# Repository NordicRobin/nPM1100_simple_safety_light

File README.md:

The nPM1100 simple safety light is a concept sketch for using the nPM1100's "ship mode" as the on/off switch for a 
rechargeable bicycle light or other small flashlight. This gives it the simple button-press activation we're used to from 
this type of device, without the need for a microcontroller. \
\
Many rechargeable bicycle lights [needs citation] use some sort of microcontroller to control the charging and on/off functionality, 
as well as different blinking modes of the LEDs on the bicycle lights. In my experience, these microcontrollers tend to drain 
the battery of the light when left unused for a period of time. By using the nPM1100's ship mode
as a power-down mode, the light consumes only 0.45 uA while powered off. This would also be the case if a microcontroller was included in the design, as the 
nPM1100 ship mode cuts power to all devices it's powering while in this mode. \
\
As an extra challenge, the nPM1100's inputs for entering and exiting ship mode have opposite polarities, therefore a simple PNP bipolar junction transistor (BJT) is included to 
flip the polarity of the button press, when the BJT is powered by the nPM1100's regulator. The BJT adds to the current consumption of the light while the circuit is powered on, 
but does not affect the 0.45 uA current draw of the system while in ship mode.

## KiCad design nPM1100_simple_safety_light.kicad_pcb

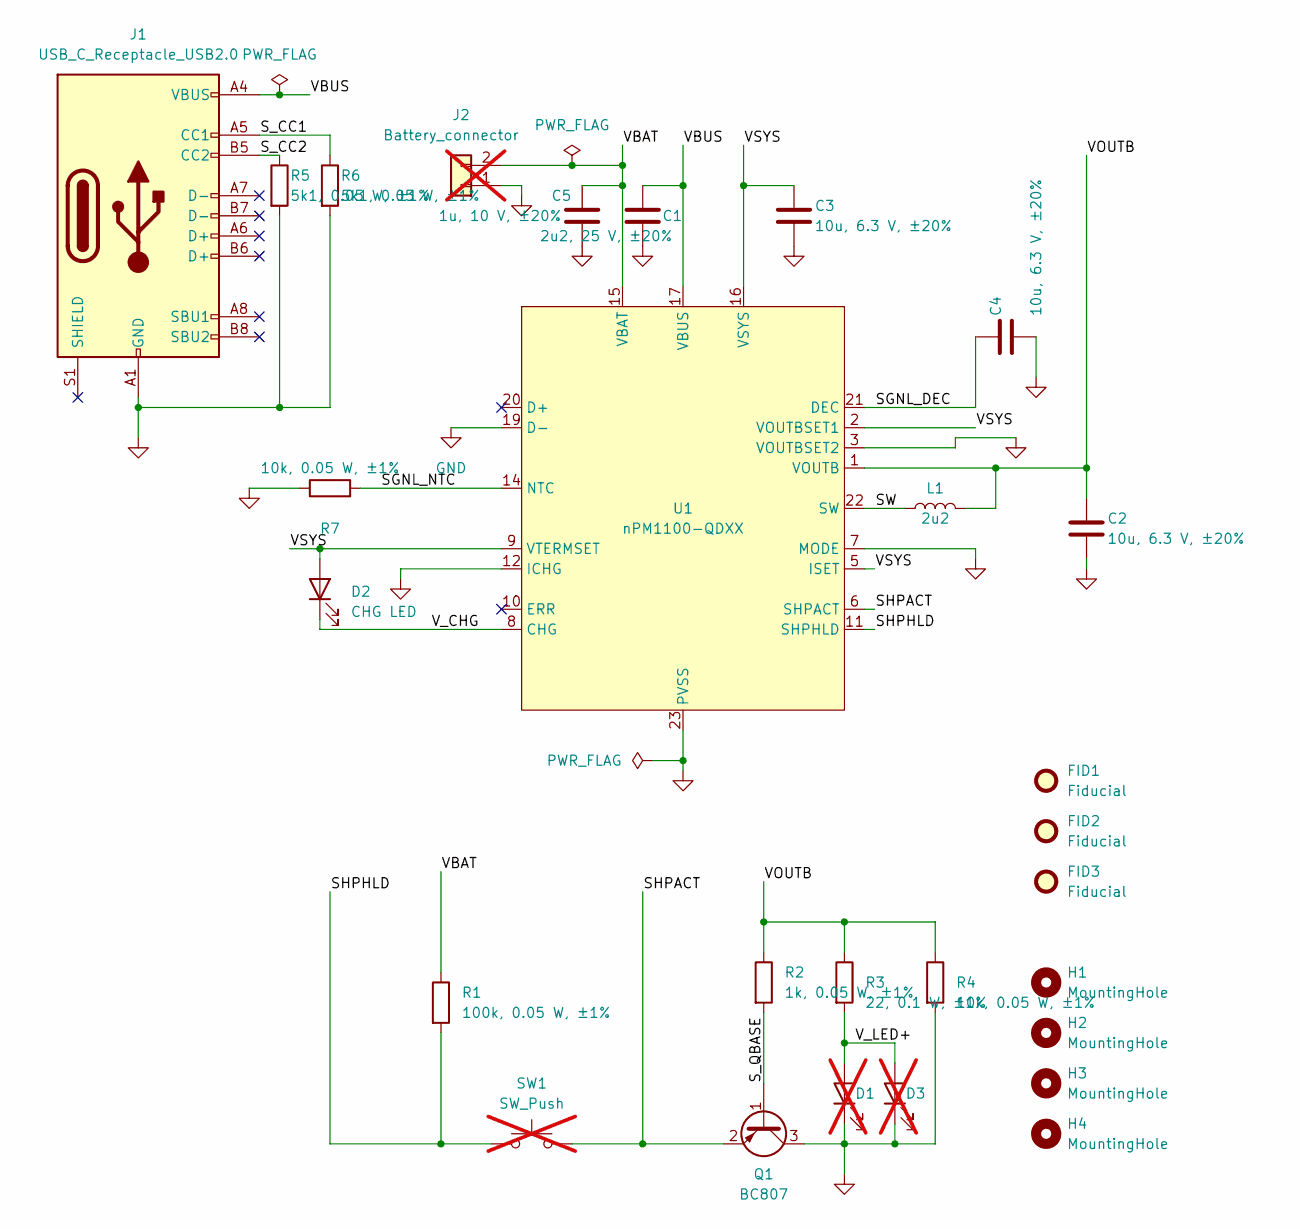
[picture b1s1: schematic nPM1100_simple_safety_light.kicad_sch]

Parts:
C1: 2u2, 25 V, ±20%; C_0603_1608Metric; Manufacturer Part Number GRM188R61E225MA12D
C2, C3, C4: 10u, 6.3 V, ±20%; C_0603_1608Metric; Manufacturer Part Number CL10A106MQ8NNNC
C5: 1u, 10 V, ±20%; C_0201_0603Metric; Manufacturer Part Number GMC02X5R105M10NT
D1, D3: POWER LED; LED_D5.0mm; not fitted
D2: CHG LED; LED_0603_1608Metric; Manufacturer Part Number LTST-C193KGKT-5A
FID1, FID2, FID3: Fiducial; Fiducial_0.75mm_Mask1.5mm
H1, H2, H3, H4: MountingHole; MountingHole_2.2mm_M2
J1: USB_C_Receptacle_USB2.0; USB_C_Receptacle_G-Switch_GT-USB-7010ASV; Manufacturer Part Number 10155435-00011LF
J2: Battery_connector; PinHeader_1x02_P2.00mm_Vertical; not fitted
L1: 2u2; L_0805_2012Metric; Manufacturer Part Number DFE201210U-2R2M
Q1: BC807; SOT-23; Manufacturer Part Number BC807-25LT1G
R1: 100k, 0.05 W, ±1%; R_0201_0603Metric; Manufacturer Part Number RC0201FR-07100KL
R2: 1k, 0.05 W, ±1%; R_0201_0603Metric; Manufacturer Part Number RC0201FR-071KL
R3: 22, 0.1 W, ±1%; R_0603_1608Metric; Manufacturer Part Number RC0603FR-1322RL
R4, R7: 10k, 0.05 W, ±1%; R_0201_0603Metric; Manufacturer Part Number RC0201FR-0710KL
R5, R6: 5k1, 0.05 W, ±1%; R_0201_0603Metric; Manufacturer Part Number RC0201FR-075K1L
SW1: SW_Push; SW_PUSH_6mm; not fitted
U1: nPM1100-QDXX; QFN-24-1EP_4x4mm_P0.5mm_EP2.6x2.6mm_ThermalVias; Manufacturer Part Number nPM1100-QDAA

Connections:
/SGNL_DEC: C4.1, U1.21 (DEC)
/SGNL_NTC: R7.2, U1.14 (NTC)
/SHPACT: Q1.2 (E), SW1.2, U1.6 (SHPACT)
/SHPHLD: R1.2, SW1.1, U1.11 (SHPHLD)
/SW: L1.1, U1.22 (SW)
/S_CC1: J1.A5 (CC1), R6.1
/S_CC2: J1.B5 (CC2), R5.1
/S_QBASE: Q1.1 (B), R2.2
/VBAT: C5.1, J2.2, R1.1, U1.15 (VBAT)
/VBUS: C1.1, J1.A4 (VBUS), J1.A9 (VBUS), J1.B4 (VBUS), J1.B9 (VBUS), U1.17 (VBUS)
/VOUTB: C2.1, L1.2, R2.1, R3.1, R4.1, U1.1 (VOUTB)
/VSYS: C3.1, D2.2 (A), U1.2 (VOUTBSET1), U1.5 (ISET), U1.9 (VTERMSET), U1.16 (VSYS)
/V_CHG: D2.1 (K), U1.8 (CHG)
/V_LED+: D1.2 (A), D3.2 (A), R3.2
GND: C1.2, C2.2, C3.2, C4.2, C5.2, D1.1 (K), D3.1 (K), J1.A1 (GND), J1.A12 (GND), J1.B1 (GND), J1.B12 (GND), J2.1, Q1.3 (C), R4.2, R5.2, R6.2, R7.1, U1.3 (VOUTBSET2), U1.7 (MODE), U1.12 (ICHG), U1.19 (D-), U1.23 (PVSS), U1.25 (PVSS)

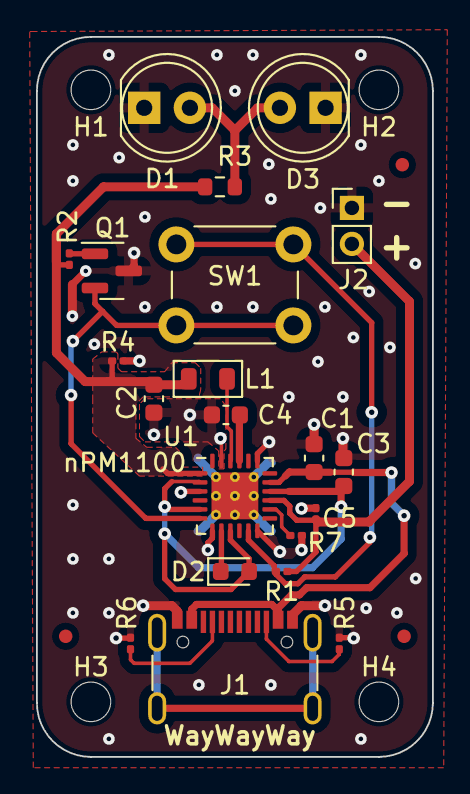
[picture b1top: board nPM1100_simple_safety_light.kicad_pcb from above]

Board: 2 copper layers, 22.0 x 40.0 mm, 28 parts (0 on the bottom side), 15 nets.

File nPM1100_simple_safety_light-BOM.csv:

"Reference","Quantity","Value","Footprint","Description","Manufacturer","Manufacturer Part Number","Distributor Link","DNP"
"C1","1","2u2, 25 V, ±20%","Capacitor_SMD:C_0603_1608Metric","Unpolarized capacitor","Murata Electronics","GRM188R61E225MA12D","https://www.digikey.no/no/products/detail/murata-electronics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",""
"C2, C3, C4","3","10u, 6.3 V, ±20%","Capacitor_SMD:C_0603_1608Metric","Unpolarized capacitor","Samsung Electro-Mechanics","CL10A106MQ8NNNC","https://www.digikey.no/no/products/detail/samsung-electro-me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",""
"C5","1","1u, 10 V, ±20%","Capacitor_SMD:C_0201_0603Metric","Unpolarized capacitor","Cal-Chip Electronics, Inc.","GMC02X5R105M10NT","https://www.digikey.no/no/products/detail/cal-chip-electroni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",""
"D2","1","CHG LED","LED_SMD:LED_0603_1608Metric","Light emitting diode","Lite-On Inc.","LTST-C193KGKT-5A","https://www.digikey.no/no/products/detail/liteon/LTST-C193KG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",""
"J1","1","USB_C_Receptacle_USB2.0","Connector_USB:USB_C_Receptacle_G-Switch_GT-USB-7010ASV","USB 2.0-only Type-C Receptacle connector","Amphenol ICC","10155435-00011LF","https://www.digikey.no/no/products/detail/amphenol-cs-fci/10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",""
"L1","1","2u2","PCM_Inductor_SMD_AKL:L_0805_2012Metric","Inductor","Murata","DFE201210U-2R2M","https://www.digikey.no/no/products/detail/murata-electronics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",""
"Q1","1","BC807","Package_TO_SOT_SMD:SOT-23","0.8A Ic, 45V Vce, PNP Transistor, SOT-23","onsemi","BC807-25LT1G","https://www.digikey.no/no/products/detail/onsemi/BC807-25LT1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",""
"R1","1","100k, 0.05 W, ±1%","Resistor_SMD:R_0201_0603Metric","Resistor","YAGEO","RC0201FR-07100KL","https://www.digikey.no/no/products/detail/yageo/RC0201FR-071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",""
"R2","1","1k, 0.05 W, ±1%","Resistor_SMD:R_0201_0603Metric","Resistor","YAGEO","RC0201FR-071KL","https://www.digikey.no/no/products/detail/yageo/RC0201FR-071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",""
"R3","1","22, 0.1 W, ±1%","Resistor_SMD:R_0603_1608Metric","Resistor","YAEGO","RC0603FR-1322RL","https://www.digikey.no/no/products/detail/yageo/RC0603FR-132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",""
"R4, R7","2","10k, 0.05 W, ±1%","Resistor_SMD:R_0201_0603Metric","Resistor","YAGEO","RC0201FR-0710KL","https://www.digikey.no/no/products/detail/yageo/RC0201FR-071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",""
"R5, R6","2","5k1, 0.05 W, ±1%","Resistor_SMD:R_0201_0603Metric","Resistor","YAGEO","RC0201FR-075K1L","https://www.digikey.no/no/products/detail/yageo/RC0201FR-075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",""
"U1","1","nPM1100-QDXX","Package_DFN_QFN:QFN-24-1EP_4x4mm_P0.5mm_EP2.6x2.6mm_ThermalVias","PMIC and Battery Charger, QFN-24","Nordic Semiconductor","NPM1100-QDAA-R","https://www.digikey.no/no/products/detail/nordic-semiconduct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",""
